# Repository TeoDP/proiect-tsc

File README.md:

# InkTime Smartwatch PCB

## General Description

This project involves the development of a PCB for an open-source smartwatch named InkTime, based on the nRF52840 microcontroller. The primary goal was to integrate all necessary components, including processing, sensors, power management, and user interface, onto a compact board that adheres to both electrical constraints and the mechanical limitations of the device housing.

The design was created using Fusion 360 Electronics, following the provided electrical schematics and laboratory layout guidelines. Significant emphasis was placed on precise routing, ground plane integrity, and component density within a limited footprint.

## Hardware Components

The system's core components include:

    - nRF52840: Main microcontroller with BLE capabilities.

    - IMU: Accelerometer and Gyroscope for motion tracking.

    - E-Paper Display: Ultra-low-power visual interface.

    - PMIC: Power Management IC for system stability.

    - Li-Po Battery: System power source.

    - USB-C: Interface for charging and power supply.

    - Haptic Motor: Vibration feedback.

Component Connectivity:

    - IMU: Connected to the MCU via I2C (SDA, SCL).

    - Display: Connected via SPI (MOSI, SCK, CS, DC, RST).

    - PMIC: Manages the entire system's power distribution.

    - USB-C: Connected directly to the charging circuitry.

    - Haptic Motor: Controlled via standard GPIO.

## Hardware Functionality

The system is centered around the nRF52840, which manages all peripherals and communications. Communication with sensors and the display is handled through standard interfaces:

    - SPI: Utilized for the display to ensure higher data transfer speeds.

    - I2C: Utilized for the IMU for simple and efficient sensor polling.

The system is powered by a Li-Po battery via a PMIC circuit that provides:

    - Voltage stabilization.

    - Overcharge/discharge protection.

    - Power distribution across all subsystems.

USB-C serves a dual purpose for battery charging and direct system power. The haptic motor provides tactile feedback and is managed by a dedicated GPIO pin.

### Estimated Consumption:

    - MCU: Low consumption in sleep mode, higher during active BLE transmission.

    - E-Paper Display: Negligible consumption (only draws power during screen updates).

    - IMU: Low power consumption over I2C.

## PCB Layout

### The PCB was designed using a 2-layer stackup:

    - Top Layer: Primary component placement and signal routing.

    - Bottom Layer: Supplementary routing and dedicated ground plane.

### Design Rules Applied:

    - Power Traces: Increased width for power lines (e.g., 3V3, VBUS).

    - Signal Traces: Minimum width of 0.15 mm.

    - Geometry: Avoided 90-degree angles to prevent signal reflection and manufacturing issues.

### Antenna Design:

    - Copper-free zone maintained directly beneath the antenna.

    - No routing allowed in the antenna keepout area to ensure signal integrity.

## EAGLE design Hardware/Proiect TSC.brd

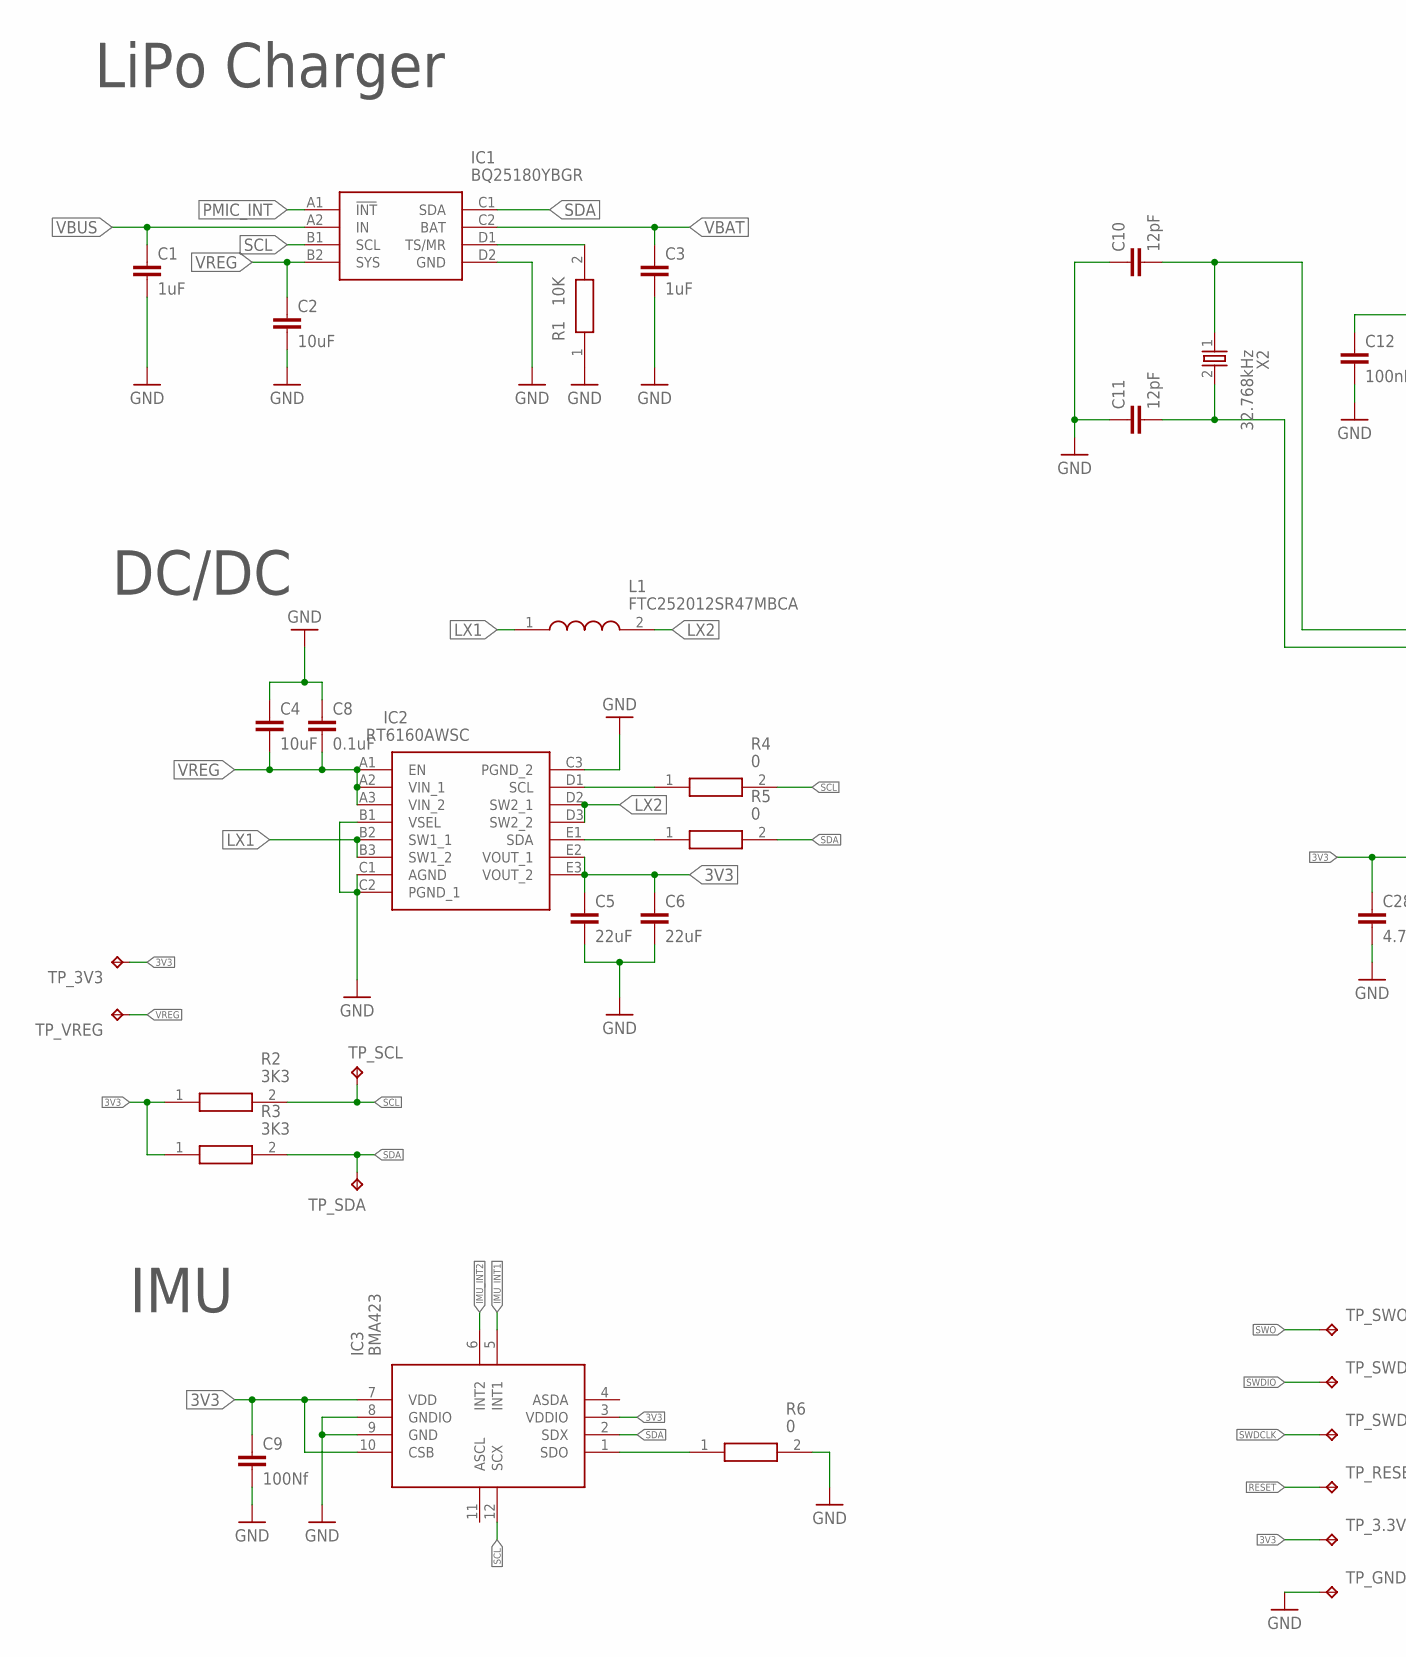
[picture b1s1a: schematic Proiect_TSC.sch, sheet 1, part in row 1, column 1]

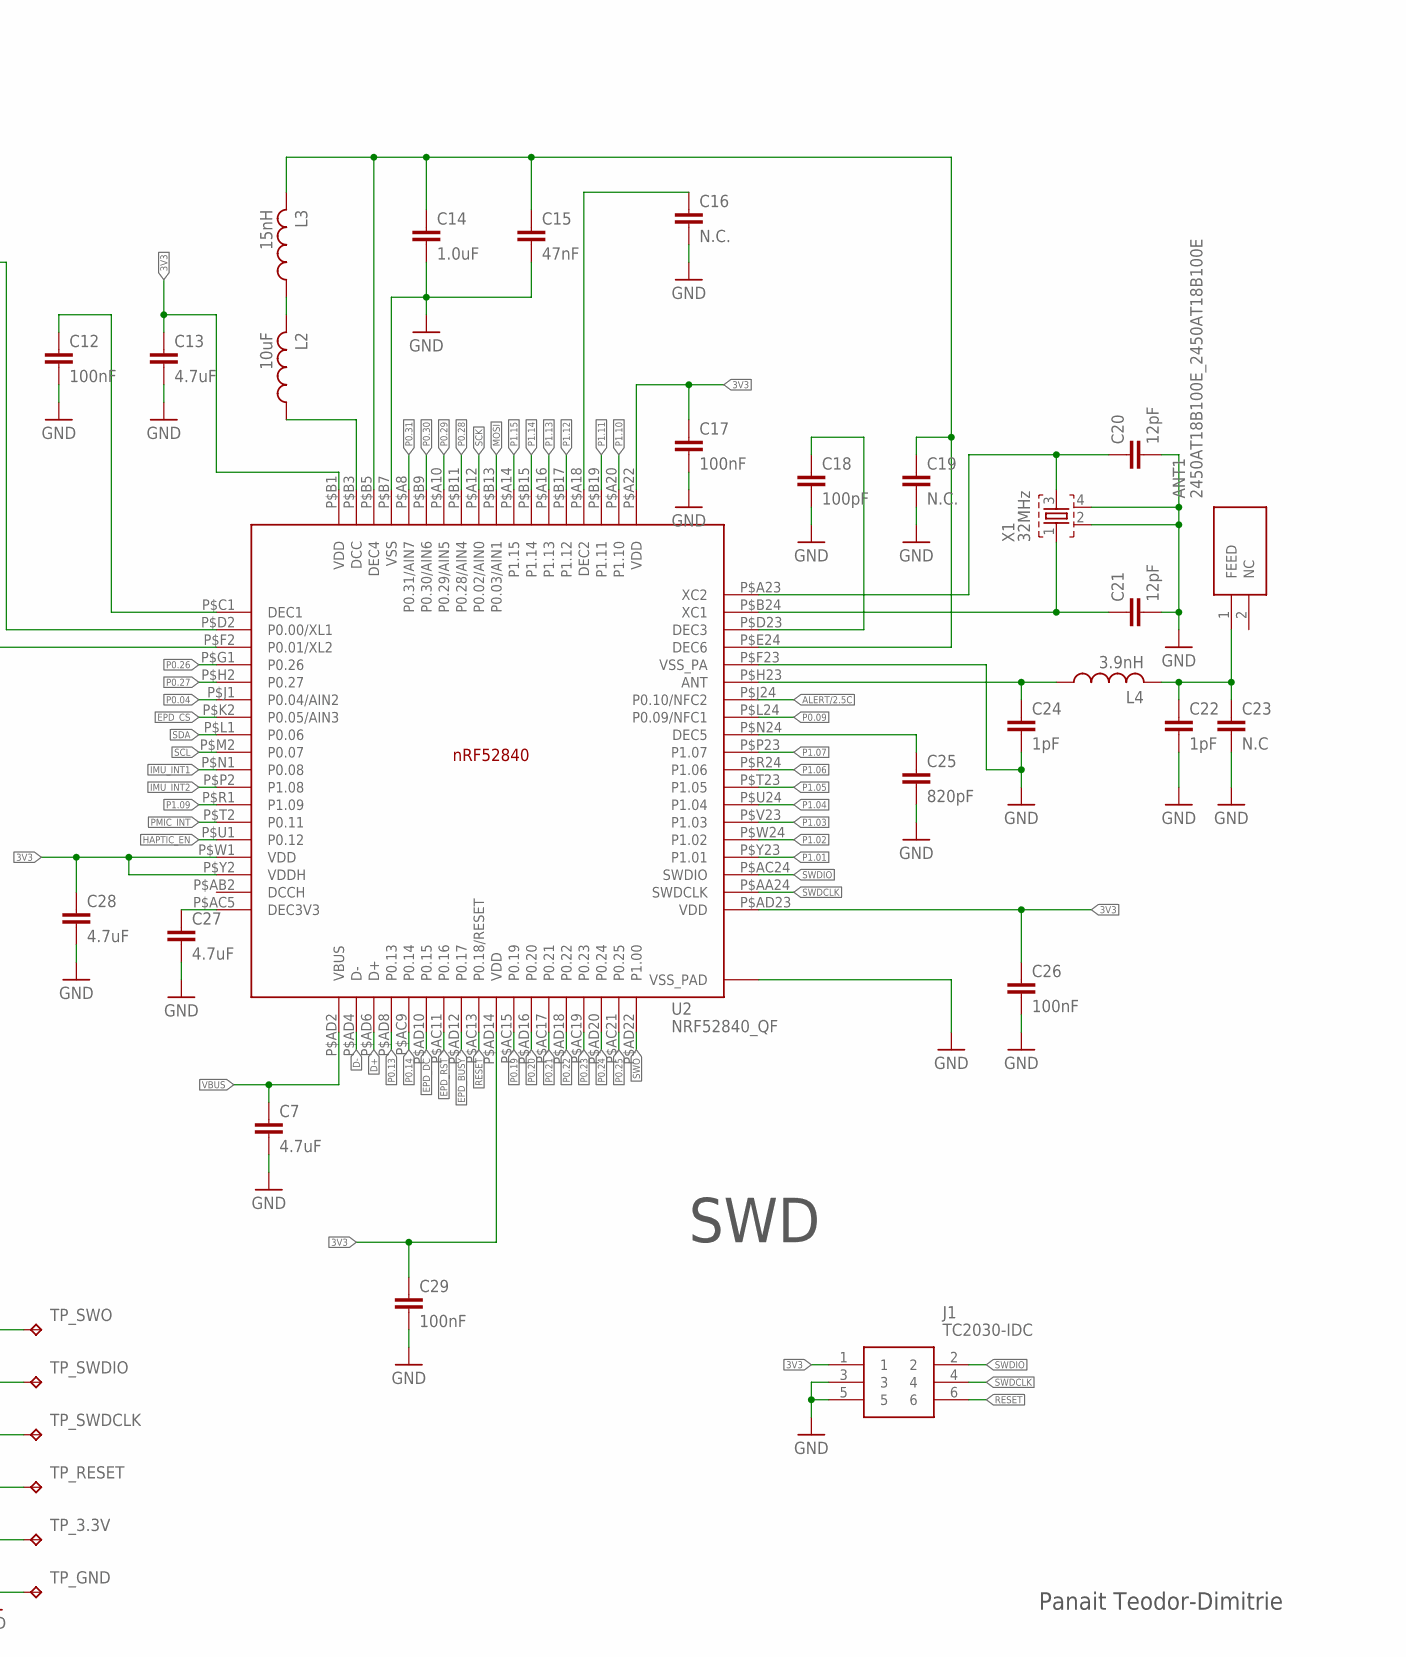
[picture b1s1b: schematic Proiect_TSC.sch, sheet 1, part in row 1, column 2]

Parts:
ANT1: 2450AT18B100E_2450AT18B100E; 2450AT18B100E_ANTC3216X140N
C1, C3: 1uF; PERFECT_0402_0402
C2, C4: 10uF; PERFECT_0402_0402
C5, C6: 22uF; PERFECT_0402_0402
C7: 4.7uF; PERFECT_0402_0402
C8: 0.1uF; NORDIC_NRF_3_RESC0201_L
C9: 100Nf; NORDIC_NRF_3_RESC0201_L
C10, C11, C20, C21: 12pF; NORDIC_NRF_3_RESC0201_L
C12, C17, C26, C29: 100nF; NORDIC_NRF_3_RESC0201_L
C13, C27, C28: 4.7uF; NORDIC_NRF_3_RESC0402_L
C14: 1.0uF; NORDIC_NRF_3_RESC0402_L
C15: 47nF; NORDIC_NRF_3_RESC0201_L
C16, C19: N.C.; NORDIC_NRF_3_RESC0201_L
C18: 100pF; NORDIC_NRF_3_RESC0201_L
C22, C24: 1pF; NORDIC_NRF_3_RESC0201_L
C23: N.C; NORDIC_NRF_3_RESC0201_L
C25: 820pF; NORDIC_NRF_3_RESC0201_L
IC1: BQ25180YBGR; BQ25180YBGR_BGA8C40P2X4_100X155X50
IC2: RT6160AWSC; RT6160AWSC_BGA15C40P3X5_140X230X60
IC3: BMA423; BMA423_BMA423
J1: TC2030-IDC; TC2030-IDC_TC2030IDC
L1: FTC252012SR47MBCA; MLP2016SR47MT0S1_INDC2016X100N
L2: 10uF; NORDIC_NRF_2_RESC0201_L
L3: 15nH; NORDIC_NRF_2_RESC0201_L
L4: 3.9nH; NORDIC_NRF_2_RESC0201_L
R1: 10K; CPF0201D7K68C1_0201
R2, R3: 3K3; CPF0201D7K68C1_0201
R4, R5, R6: 0; CPF0201D7K68C1_0201
TP_3.3V, TP_3V3: HECTOR_WATCH_1_TPTP20R; HECTOR_WATCH_1_TP20R
TP_GND: HECTOR_WATCH_1_TPTP20R; HECTOR_WATCH_1_TP20R
TP_RESET: HECTOR_WATCH_1_TPTP20R; HECTOR_WATCH_1_TP20R
TP_SCL: HECTOR_WATCH_1_TPTP20R; HECTOR_WATCH_1_TP20R
TP_SDA: HECTOR_WATCH_1_TPTP20R; HECTOR_WATCH_1_TP20R
TP_SWDCLK: HECTOR_WATCH_1_TPTP20R; HECTOR_WATCH_1_TP20R
TP_SWDIO: HECTOR_WATCH_1_TPTP20R; HECTOR_WATCH_1_TP20R
TP_SWO: HECTOR_WATCH_1_TPTP20R; HECTOR_WATCH_1_TP20R
TP_VREG: HECTOR_WATCH_1_TPTP20R; HECTOR_WATCH_1_TP20R
U2: NRF52840_QF; NORDIC_NRF_4_AQFN50P700X700X85_HS-74N
X1: 32MHz; NORDIC_NRF_BT-XTAL_2016_N
X2: 32.768kHz; NORDIC_NRF_1_XTAL_3215_N

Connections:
3V3: C5.1, C6.1, C9.1, C13.1, C17.1, C26.1, C28.1, C29.1, IC2.E2 (VOUT_1), IC2.E3 (VOUT_2), IC3.3 (VDDIO), IC3.7 (VDD), IC3.10 (CSB), J1.1, R2.1, R3.1, TP_3.3V.TP, TP_3V3.TP, U2.P$A22 (VDD), U2.P$AD14 (VDD), U2.P$AD23 (VDD), U2.P$B1 (VDD), U2.P$W1 (VDD), U2.P$Y2 (VDDH); also elsewhere on the board
ALERT/2.5C: U2.P$J24 (P0.10/NFC2)
D+: U2.P$AD6 (D+); also elsewhere on the board
D-: U2.P$AD4 (D-); also elsewhere on the board
EPD_BUSY: U2.P$AD12 (P0.17); also elsewhere on the board
EPD_CS: U2.P$K2 (P0.05/AIN3); also elsewhere on the board
EPD_DC: U2.P$AD10 (P0.15); also elsewhere on the board
EPD_RST: U2.P$AC11 (P0.16); also elsewhere on the board
GND: C1.2, C2.2, C3.2, C4.1, C5.2, C6.2, C7.2, C8.1, C9.2, C10.1, C11.1, C12.2, C13.2, C14.2, C15.2, C16.2, C17.2, C18.2, C19.2, C20.2, C21.2, C22.2, C23.2, C24.2, C25.2, C26.2, C27.2, C28.2, C29.2, IC1.D2 (GND), IC2.B1 (VSEL), IC2.C1 (AGND), IC2.C2 (PGND_1), IC2.C3 (PGND_2), IC3.8 (GNDIO), IC3.9 (GND), J1.3, J1.5, R1.1, R6.2, TP_GND.TP, U2.P$74 (VSS_PAD), U2.P$75 (VSS_PAD), U2.P$76 (VSS_PAD), U2.P$77 (VSS_PAD), U2.P$78 (VSS_PAD), U2.P$79 (VSS_PAD), U2.P$80 (VSS_PAD), U2.P$81 (VSS_PAD), U2.P$82 (VSS_PAD), U2.P$83 (VSS_PAD), U2.P$84 (VSS_PAD), U2.P$85 (VSS_PAD), U2.P$86 (VSS_PAD), U2.P$87 (VSS_PAD), U2.P$88 (VSS_PAD), U2.P$89 (VSS_PAD), U2.P$90 (VSS_PAD), U2.P$B7 (VSS), U2.P$F23 (VSS_PA), X1.2, X1.4; also elsewhere on the board
HAPTIC_EN: U2.P$U1 (P0.12); also elsewhere on the board
IMU_INT1: IC3.5 (INT1), U2.P$N1 (P0.08)
IMU_INT2: IC3.6 (INT2), U2.P$P2 (P1.08)
LX1: IC2.B2 (SW1_1), IC2.B3 (SW1_2), L1.1
LX2: IC2.D2 (SW2_1), IC2.D3 (SW2_2), L1.2
MOSI: U2.P$B13 (P0.03/AIN1); also elsewhere on the board
unnamed: ANT1.1 (FEED), C22.1, C23.1, L4.2
unnamed: IC1.D1 (TS/MR), R1.2
unnamed: C20.1, U2.P$A23 (XC2), X1.3
unnamed: IC2.D1 (SCL), R4.1
unnamed: C12.1, U2.P$C1 (DEC1)
unnamed: IC2.E1 (SDA), R5.1
unnamed: C10.2, U2.P$D2 (P0.00/XL1), X2.1
unnamed: C11.2, U2.P$F2 (P0.01/XL2), X2.2
unnamed: IC3.1 (SDO), R6.1
unnamed: L2.2, L3.1
unnamed: C14.1, C15.1, C19.1, L3.2, U2.P$B5 (DEC4), U2.P$E24 (DEC6)
unnamed: C21.1, U2.P$B24 (XC1), X1.1
unnamed: L2.1, U2.P$B3 (DCC)
unnamed: C18.1, U2.P$D23 (DEC3)
unnamed: C24.1, L4.1, U2.P$H23 (ANT)
unnamed: C27.1, U2.P$AC5 (DEC3V3)
unnamed: C25.1, U2.P$N24 (DEC5)
unnamed: C16.1, U2.P$A18 (DEC2)
P0.04: U2.P$J1 (P0.04/AIN2)
P0.09: U2.P$L24 (P0.09/NFC1)
P0.13: U2.P$AD8 (P0.13); also elsewhere on the board
P0.14: U2.P$AC9 (P0.14)
P0.19: U2.P$AC15 (P0.19)
P0.20: U2.P$AD16 (P0.20)
P0.21: U2.P$AC17 (P0.21)
P0.22: U2.P$AD18 (P0.22)
P0.23: U2.P$AC19 (P0.23)
P0.24: U2.P$AD20 (P0.24)
P0.25: U2.P$AC21 (P0.25)
P0.26: U2.P$G1 (P0.26)
P0.27: U2.P$H2 (P0.27)
P0.28: U2.P$B11 (P0.28/AIN4)
P0.29: U2.P$A10 (P0.29/AIN5)
P0.30: U2.P$B9 (P0.30/AIN6)
P0.31: U2.P$A8 (P0.31/AIN7)
P1.01: U2.P$Y23 (P1.01); also elsewhere on the board
P1.02: U2.P$W24 (P1.02); also elsewhere on the board
P1.03: U2.P$V23 (P1.03)
P1.04: U2.P$U24 (P1.04)
P1.05: U2.P$T23 (P1.05)
P1.06: U2.P$R24 (P1.06)
P1.07: U2.P$P23 (P1.07)
P1.09: U2.P$R1 (P1.09)
P1.10: U2.P$A20 (P1.10)
P1.11: U2.P$B19 (P1.11)
P1.12: U2.P$B17 (P1.12)
P1.13: U2.P$A16 (P1.13)
P1.14: U2.P$B15 (P1.14); also elsewhere on the board
P1.15: U2.P$A14 (P1.15)
PMIC_INT: IC1.A1 (!INT), U2.P$T2 (P0.11)
RESET: J1.6, TP_RESET.TP, U2.P$AC13 (P0.18/RESET)
SCK: U2.P$A12 (P0.02/AIN0); also elsewhere on the board
SCL: IC1.B1 (SCL), IC3.12 (SCX), R2.2, R4.2, TP_SCL.TP, U2.P$M2 (P0.07); also elsewhere on the board
SDA: IC1.C1 (SDA), IC3.2 (SDX), R3.2, R5.2, TP_SDA.TP, U2.P$L1 (P0.06); also elsewhere on the board
SWDCLK: J1.4, TP_SWDCLK.TP, U2.P$AA24 (SWDCLK)
SWDIO: J1.2, TP_SWDIO.TP, U2.P$AC24 (SWDIO)
SWO: TP_SWO.TP, U2.P$AD22 (P1.00)
VBAT: C3.1, IC1.C2 (BAT); also elsewhere on the board
VBUS: C1.1, C7.1, IC1.A2 (IN), U2.P$AD2 (VBUS); also elsewhere on the board
VREG: C2.1, C4.2, C8.2, IC1.B2 (SYS), IC2.A1 (EN), IC2.A2 (VIN_1), IC2.A3 (VIN_2), TP_VREG.TP

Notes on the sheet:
LiPo Charger
DC/DC
IMU
SWD
Panait Teodor-Dimitrie

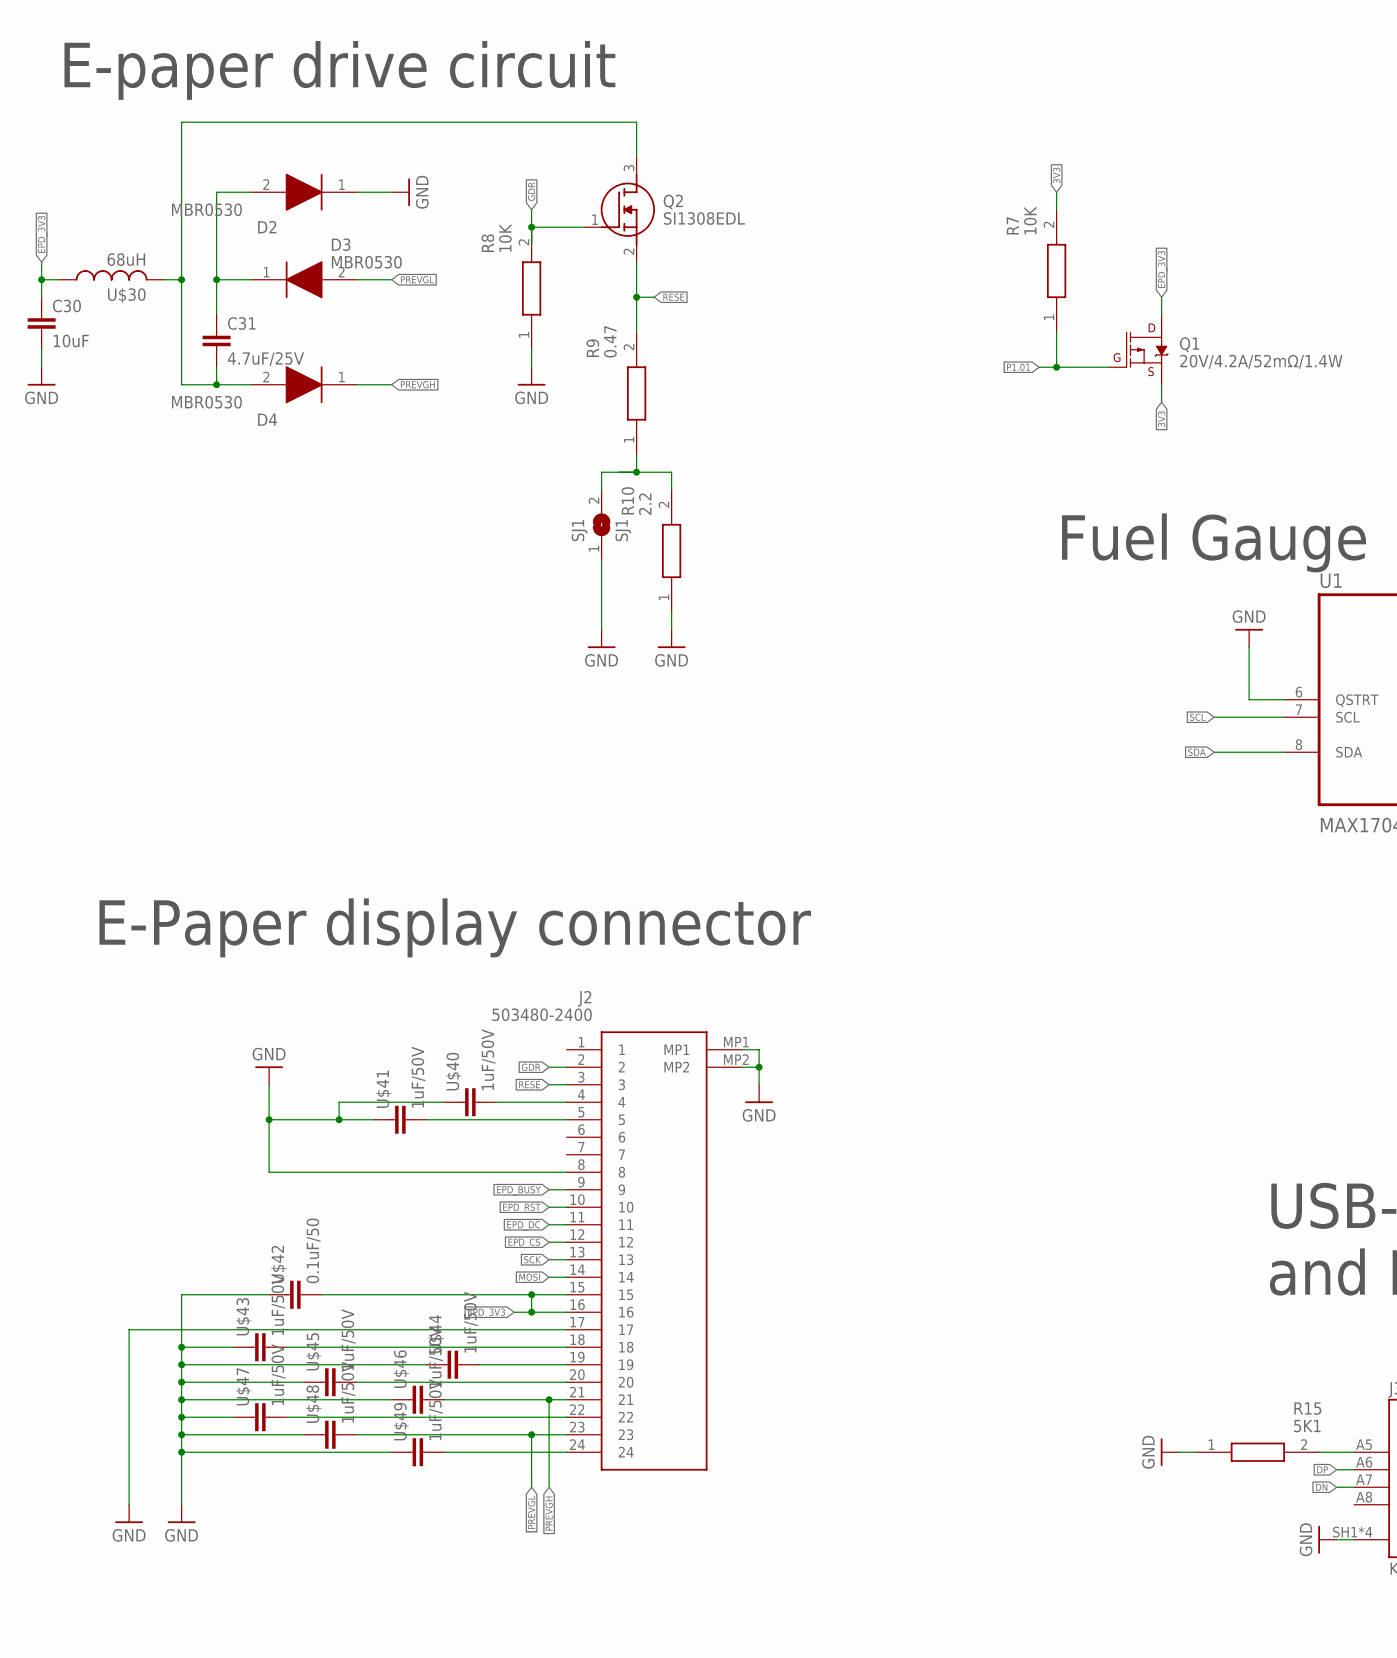
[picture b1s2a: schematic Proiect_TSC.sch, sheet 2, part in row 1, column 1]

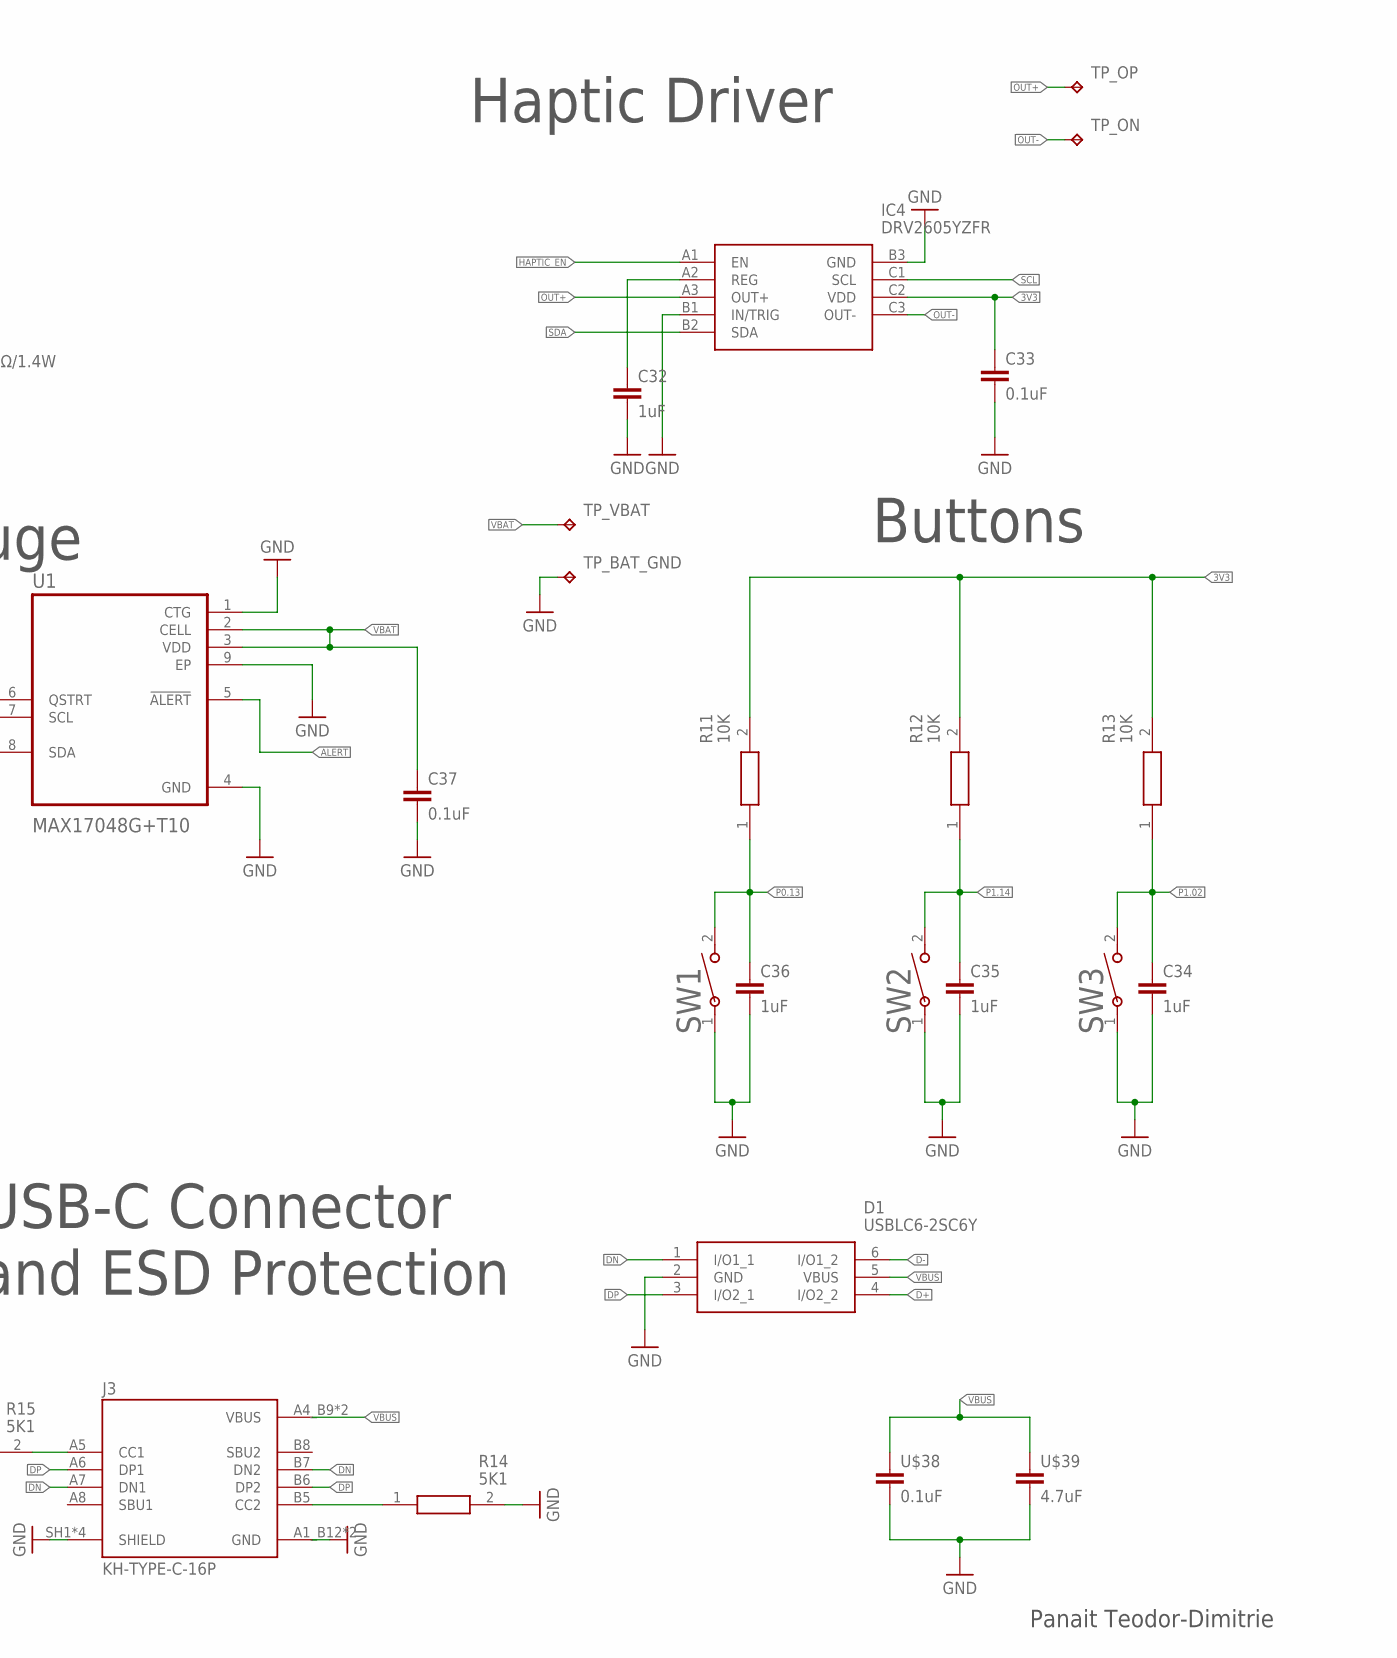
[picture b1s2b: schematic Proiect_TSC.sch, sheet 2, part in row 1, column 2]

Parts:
C30: 10uF; NORDIC_NRF_3_RESC0402_L
C31: 4.7uF/25V; NORDIC_NRF_3_RESC0402_L
C32, C34, C35, C36: 1uF; NORDIC_NRF_3_RESC0402_L
C33, C37: 0.1uF; NORDIC_NRF_3_RESC0201_L
D1: USBLC6-2SC6Y; ESP32_C6_LIBRARY_3_SOT95P280X145-6N
D2, D3, D4: MBR0530; ESP32_C6_LIBRARY_5_SOD3716X135N
IC4: DRV2605YZFR; DRV2605YZFR_BGA9C50P3X3_144X144X62
J2: 503480-2400; 503480-2400_5034802400
J3: KH-TYPE-C-16P; KH-TYPE-C-16P_KINGHELM_KH-TYPE-C-16P
Q1: 20V/4.2A/52mΩ/1.4W; ESP32_C6_LIBRARY_4_ESP32_C6_LIBRARY_4_ESP32_C6_LIBRARY_4_ES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
Q2: SI1308EDL; ESP32_C6_LIBRARY_6_SOT65P210X110-3N
R7, R8, R11, R12, R13: 10K; CPF0201D7K68C1_0201
R9: 0.47; CPF0201D7K68C1_0201
R10: 2.2; CPF0201D7K68C1_0201
R14, R15: 5K1; CPF0201D7K68C1_0201
SJ1: SJ1; ESP32_C6_LIBRARY_7_JUMPER_SJ
SW1: SW1; 2025-10-22_07-23-44_LIBRARY_SW_EVP-AKE31A_PAN
SW2, SW3: 2025-10-22_07-23-44_LIBRARY_EVP-AKE31ASW_EVP-AKE3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; 2025-10-22_07-23-44_LIBRARY_SW_EVP-AKE31A_PAN
TP_BAT_GND: HECTOR_WATCH_1_TPTP20R; HECTOR_WATCH_1_TP20R
TP_ON: HECTOR_WATCH_1_TPTP20R; HECTOR_WATCH_1_TP20R
TP_OP: HECTOR_WATCH_1_TPTP20R; HECTOR_WATCH_1_TP20R
TP_VBAT: HECTOR_WATCH_1_TPTP20R; HECTOR_WATCH_1_TP20R
U1: MAX17048G+T10; ESP32_C6_LIBRARY_SON50P200X200X80-9N
U$30: 68uH; NORDIC_NRF_2_RESC0201_L
U$38: 0.1uF; NORDIC_NRF_3_RESC0201_L
U$39: 4.7uF; NORDIC_NRF_3_RESC0402_L
U$40, U$41, U$43, U$44, U$45, U$46, U$47, U$48, U$49: 1uF/50V; NORDIC_NRF_3_RESC0402_L
U$42: 0.1uF/50; NORDIC_NRF_3_RESC0201_L

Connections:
3V3: C33.1, IC4.C2 (VDD), Q1.2 (S), R7.2, R11.2, R12.2, R13.2; also elsewhere on the board
ALERT: U1.5 (!ALERT)
D+: D1.4 (I/O2_2); also elsewhere on the board
D-: D1.6 (I/O1_2); also elsewhere on the board
DN: D1.1 (I/O1_1), J3.A7 (DN1), J3.B7 (DN2)
DP: D1.3 (I/O2_1), J3.A6 (DP1), J3.B6 (DP2)
EPD_3V3: C30.1, J2.15, J2.16, Q1.3 (D), U$30.1, U$42.2
EPD_BUSY: J2.9; also elsewhere on the board
EPD_CS: J2.12; also elsewhere on the board
EPD_DC: J2.11; also elsewhere on the board
EPD_RST: J2.10; also elsewhere on the board
GDR: J2.2, Q2.1 (G), R8.2
GND: C30.2, C32.2, C33.2, C34.2, C35.2, C36.2, C37.2, D1.2 (GND), D2.1 (K), IC4.B1 (IN/TRIG), IC4.B3 (GND), J2.8, J2.17, J2.MP1, J2.MP2, J3.A1_B12 (GND), J3.A12_B1 (GND), J3.SH1 (SHIELD), J3.SH2 (SHIELD), J3.SH3 (SHIELD), J3.SH4 (SHIELD), R8.1, R10.1, R14.2, R15.1, SJ1.1, SW1.1, SW2.1, SW3.1, TP_BAT_GND.TP, U1.1 (CTG), U1.4 (GND), U1.6 (QSTRT), U1.9 (EP), U$38.2, U$39.2, U$40.1, U$41.1, U$42.1, U$43.1, U$44.1, U$45.1, U$46.1, U$47.1, U$48.1, U$49.1; also elsewhere on the board
HAPTIC_EN: IC4.A1 (EN); also elsewhere on the board
MOSI: J2.14; also elsewhere on the board
unnamed: C31.1, D2.2 (A), D3.1 (K)
unnamed: C31.2, D4.2 (A), Q2.3 (D), U$30.2
unnamed: C32.1, IC4.A2 (REG)
unnamed: J2.4, U$40.2
unnamed: J2.5, U$41.2
unnamed: J3.A5 (CC1), R15.2
unnamed: R9.1, R10.2, SJ1.2
unnamed: J2.18, U$43.2
unnamed: J2.19, U$44.2
unnamed: J2.20, U$45.2
unnamed: J2.22, U$47.2
unnamed: J2.24, U$49.2
unnamed: J3.B5 (CC2), R14.1
OUT+: IC4.A3 (OUT+), TP_OP.TP
OUT-: IC4.C3 (OUT-), TP_ON.TP
P0.13: C36.1, R11.1, SW1.2; also elsewhere on the board
P1.01: Q1.1 (G), R7.1; also elsewhere on the board
P1.02: C34.1, R13.1, SW3.2; also elsewhere on the board
P1.14: C35.1, R12.1, SW2.2; also elsewhere on the board
PREVGH: D4.1 (K), J2.21, U$46.2
PREVGL: D3.2 (A), J2.23, U$48.2
RESE: J2.3, Q2.2 (S), R9.2
SCK: J2.13; also elsewhere on the board
SCL: IC4.C1 (SCL), U1.7 (SCL); also elsewhere on the board
SDA: IC4.B2 (SDA), U1.8 (SDA); also elsewhere on the board
VBAT: C37.1, TP_VBAT.TP, U1.2 (CELL), U1.3 (VDD); also elsewhere on the board
VBUS: D1.5 (VBUS), J3.A4_B9 (VBUS), J3.A9_B4 (VBUS), U$38.1, U$39.1; also elsewhere on the board

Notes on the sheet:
E-paper drive circuit
Fuel Gauge
Haptic Driver
E-Paper display connector
Buttons
USB-C Connector and ESD Protection
Panait Teodor-Dimitrie

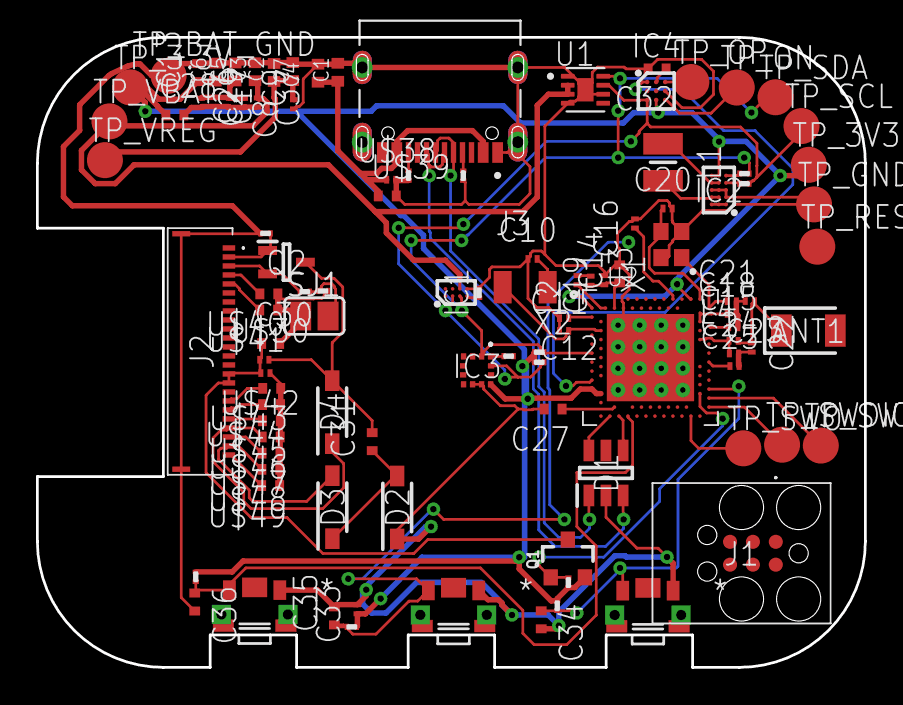
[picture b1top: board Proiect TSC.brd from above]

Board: 2 copper layers, 46.0 x 35.0 mm, 105 parts (0 on the bottom side), 69 nets.

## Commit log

2026-04-15 Add .sch and .brd files
    First revision, many this still due to change
2026-04-20 WIP commit. Still adding features
2026-04-20 Finished 2D manufacturing
2026-04-20 Add License and Readme files

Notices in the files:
parts and their libraries:
COPYRIGHT: Copyright (C) 2025 Ultra Librarian. All rights reserved.
